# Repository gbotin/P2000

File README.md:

Infos :
Stepper : 28byj-48

http://suncalc.net/#/50.6244,2.6875,9/2023.12.01/15:34

FIFO readings
https://github.com/rlogiacco/CircularBuffer

https://github.com/adafruit/RTClib

### TODO :
- update stepper lib to accelstepper
- buy rtc module
- homing step motor - buy homing switch

### Utils :
- Read current time : echo "time_print" > /dev/tty.usbserial-1230
- Send current time : echo "time_set $(date +%s)" > /dev/tty.usbserial-1440
- Reset EEPROM : echo 'eeprom_reset' > /dev/tty.usbserial-1230

### Infos :
- Stepper : 28byj-48

### FIFO readings info
- https://github.com/rlogiacco/CircularBuffer

### Libs 

- https://github.com/PaulStoffregen/Time
- http://github.com/JChristensen/Timezone
- https://github.com/arduino-libraries/Stepper
- https://github.com/dmkishi/Dusk2Dawn

### Power Consumption

Mode SET idle : 0.0358V
Motor running 

sleep 0.146

max 0.2620

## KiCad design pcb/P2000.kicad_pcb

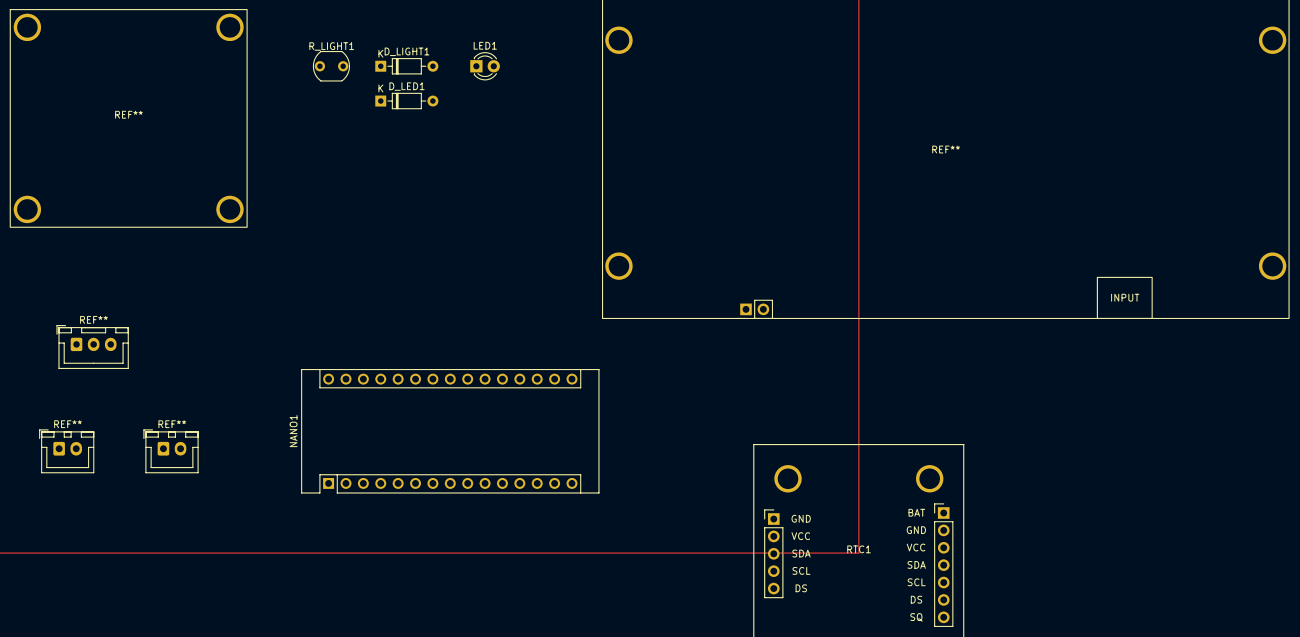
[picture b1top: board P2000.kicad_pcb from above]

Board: 2 copper layers, 6 parts (0 on the bottom side), 8 nets, no tracks yet.

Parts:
D_LED1: 1N4148; D_DO-35_SOD27_P7.62mm_Horizontal
D_LIGHT1: 1N4148; D_DO-35_SOD27_P7.62mm_Horizontal
LED1: LED; LED_D3.0mm_Clear
NANO1: Arduino_Nano_v3.x; Arduino_Nano
RTC1: DS1307+; DS1307
R_LIGHT1: LDR07; R_LDR_5.1x4.3mm_P3.4mm_Vertical

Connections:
GND: LED1.1 (K), NANO1.4 (GND), RTC1.4 (GND)
unnamed: D_LED1.1 (K), LED1.2 (A)
unnamed: D_LED1.2 (A), NANO1.12 (D9)
unnamed: D_LIGHT1.1 (K), NANO1.19 (A0)
unnamed: D_LIGHT1.2 (A), R_LIGHT1.2
unnamed: NANO1.23 (A4), RTC1.5 (SDA)
unnamed: NANO1.24 (A5), RTC1.6 (SCL)
unnamed: NANO1.27 (+5V), RTC1.8 (VCC), R_LIGHT1.1

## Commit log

2021-04-23 Add Readme to repo
2021-05-23 AccelStepper OK
2021-05-24 Buttons control OK
2022-10-02 Update controls + read/write eeprom
2022-10-02 WIP code refac
2022-10-08 Door controls OK
2022-10-09 system time set ok
2022-10-09 sunrise/sunset management
2023-03-18 Tests after motor perf problems
2023-03-18 Finishing door controls
2023-03-18 WIP open/closing times
2023-03-19 Add scenario command
2023-03-19 WIP time refac
2023-03-25 Defines cleanup
2023-03-25 Finishing time refac
2023-03-26 Add command feature and refac
2023-04-10 Add state control to led
2023-04-10 Finishing auto door control via time
2023-04-10 Add mode management and toggle door action
2023-04-13 Add RTC controller
2023-04-14 Fix motor power consumption
2023-12-31 Start planning PCB
